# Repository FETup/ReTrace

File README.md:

# ReTrace

ReTrace is a watch mod for the infamous Casio F-91W. Inspired by [CarrotIndustries Pluto mod](https://github.com/carrotIndustries/pluto). Borrowed his PCB design as its well done
and tested. Replaced the MSP430 controller with PIC24.

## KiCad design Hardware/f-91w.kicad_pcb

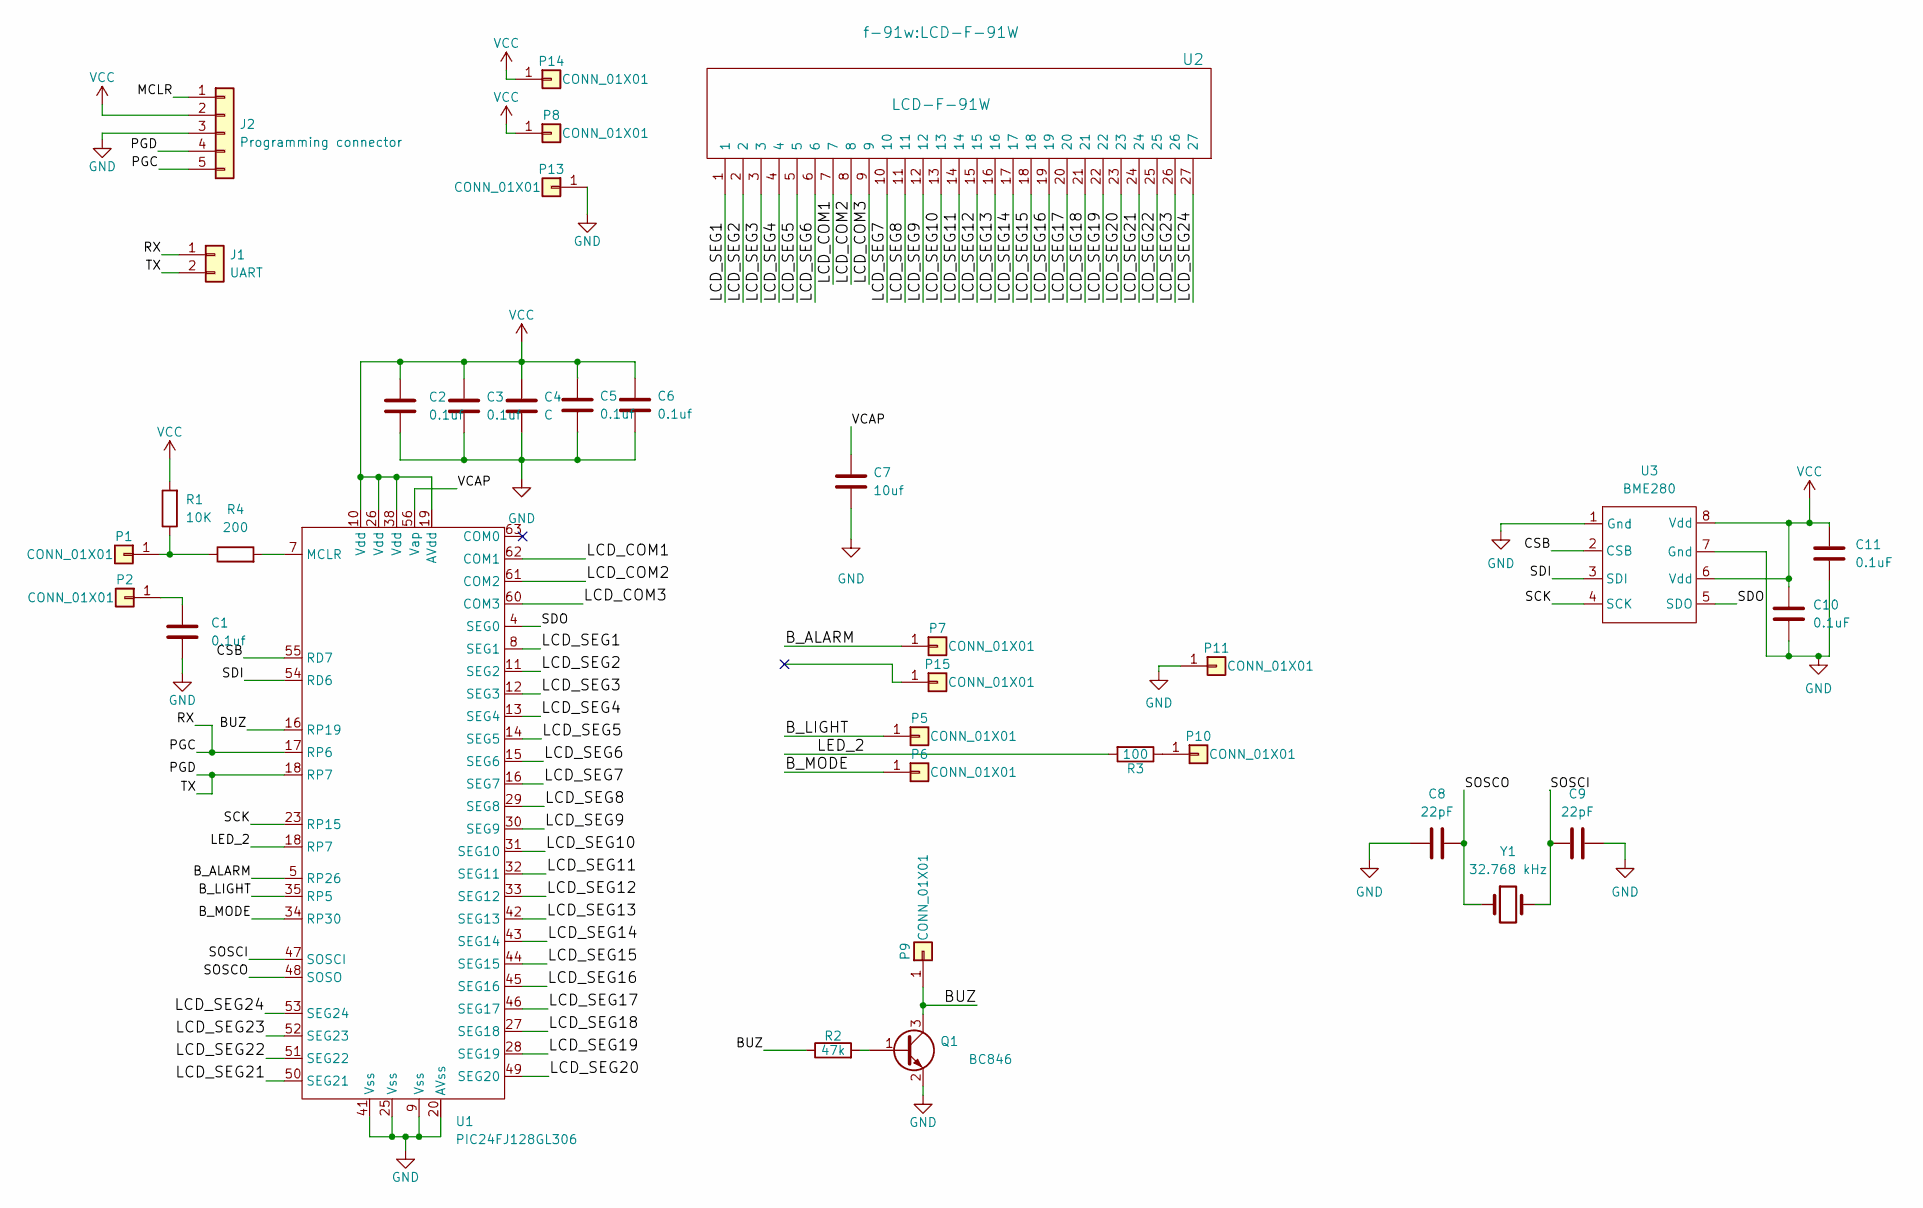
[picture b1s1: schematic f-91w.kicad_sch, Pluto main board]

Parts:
C1, C2, C3, C5, C6: 0.1uf; C_0402_1005Metric
C4: C; C_0402_1005Metric
C7: 10uf; C_0402_1005Metric
C8, C9: 22pF; C_0402_1005Metric
C10, C11: 0.1uF; C_0402_1005Metric
J1: UART; PinHeader_1x02_P1.00mm_Vertical
J2: Programming connector; PinHeader_1x05_P1.00mm_Vertical
P1, P2, P5, P6, P7, P8, P9, P10, P11, P13, P14, P15: CONN_01X01; 1pin
Q1: BC846; SOT-23
R1: 10K; R_0402_1005Metric
R2: 47k; R_0402
R3: 100; R_0402
R4: 200; R_0402_1005Metric
U1: PIC24FJ128GL306; QFN-64-1EP_9x9mm_P0.5mm_EP7.5x7.5mm
U2: LCD-F-91W
U3: BME280; Bosch_LGA-8_2.5x2.5mm_P0.65mm_ClockwisePinNumbering
Y1: 32.768 kHz; Crystal_SMD_EuroQuartz_EQ161-2Pin_3.2x1.5mm

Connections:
/B_ALARM: P7.1, U1.5 (RP26)
/B_LIGHT: P5.1, U1.35 (RP5)
/B_MODE: P6.1, U1.34 (RP30)
/CSB: U1.55 (RD7), U3.2 (CSB)
/LCD_COM1: U1.62 (COM1), U2.7
/LCD_COM2: U1.61 (COM2), U2.8
/LCD_COM3: U1.60 (COM3), U2.9
/LCD_SEG1: U1.8 (SEG1), U2.1
/LCD_SEG2: U1.11 (SEG2), U2.2
/LCD_SEG3: U1.12 (SEG3), U2.3
/LCD_SEG4: U1.13 (SEG4), U2.4
/LCD_SEG5: U1.14 (SEG5), U2.5
/LCD_SEG6: U1.15 (SEG6), U2.6
/LCD_SEG8: U1.29 (SEG8), U2.11
/LCD_SEG9: U1.30 (SEG9), U2.12
/LCD_SEG10: U1.31 (SEG10), U2.13
/LCD_SEG11: U1.32 (SEG11), U2.14
/LCD_SEG12: U1.33 (SEG12), U2.15
/LCD_SEG13: U1.42 (SEG13), U2.16
/LCD_SEG14: U1.43 (SEG14), U2.17
/LCD_SEG15: U1.44 (SEG15), U2.18
/LCD_SEG16: U1.45 (SEG16), U2.19
/LCD_SEG17: U1.46 (SEG17), U2.20
/LCD_SEG18: U1.27 (SEG18), U2.21
/LCD_SEG19: U1.28 (SEG19), U2.22
/LCD_SEG20: U1.49 (SEG20), U2.23
/LCD_SEG21: U1.50 (SEG21), U2.24
/LCD_SEG22: U1.51 (SEG22), U2.25
/LCD_SEG23: U1.52 (SEG23), U2.26
/LCD_SEG24: U1.53 (SEG24), U2.27
/MCLR: J2.1
/PGC: J1.1, J2.5, U1.17 (RP6)
/SCK: U1.23 (RP15), U3.4 (SCK)
/SDI: U1.54 (RD6), U3.3 (SDI)
/SDO: U1.4 (SEG0), U3.5 (SDO)
/SOSCI: C9.1, U1.47 (SOSCI), Y1.2
/SOSCO: C8.2, U1.48 (SOSO), Y1.1
/VCAP: C7.1, U1.56 (Vap)
GND: C1.2, C2.2, C3.2, C4.2, C5.2, C6.2, C7.2, C8.1, C9.2, C10.2, C11.2, J2.3, P11.1, P13.1, Q1.2 (E), U1.9 (Vss), U1.20 (AVss), U1.25 (Vss), U1.41 (Vss), U3.1 (Gnd), U3.7 (Gnd)
unnamed: C1.1, P2.1
unnamed: P1.1, R1.1, R4.1
unnamed: P10.1, R3.1
unnamed: Q1.1 (B), R2.2
unnamed: R4.2, U1.7 (MCLR)
VCC: C2.1, C3.1, C4.1, C5.1, C6.1, C10.1, C11.1, J2.2, P8.1, P14.1, R1.2, U1.10 (Vdd), U1.19 (AVdd), U1.26 (Vdd), U1.38 (Vdd), U3.6 (Vdd), U3.8 (Vdd)

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
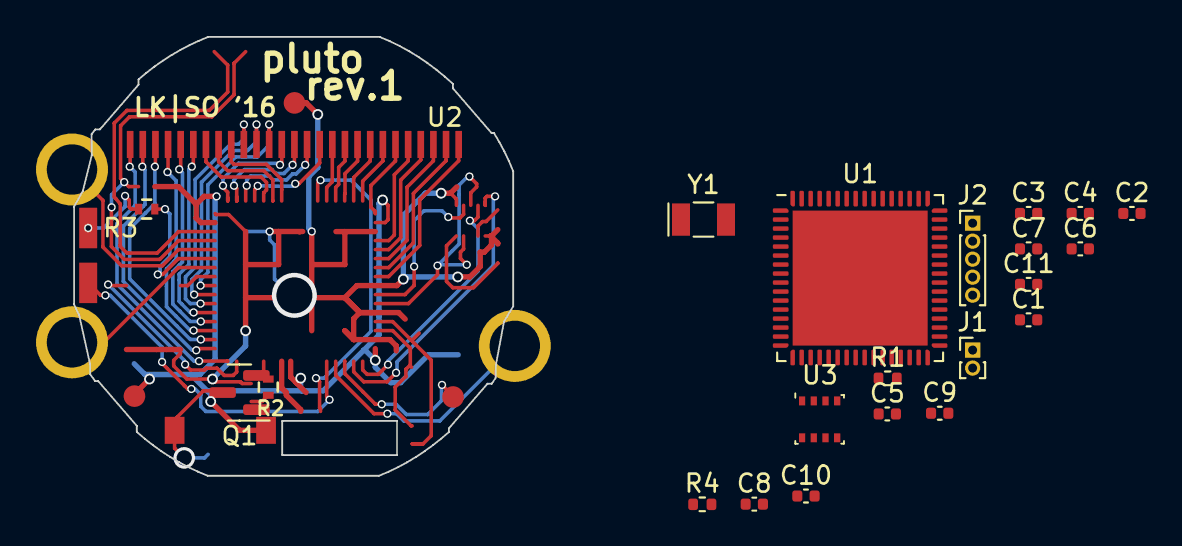
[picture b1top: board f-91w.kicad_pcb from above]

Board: 2 copper layers, 24.4 x 24.4 mm, 32 parts (0 on the bottom side), 46 nets.

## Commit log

2022-06-17 Update Schematic and Add PIC and BME280 symbols
2022-06-19 Add PIC and BME in schematic
2022-06-20 Add temporary symbols to check
2022-06-21 Add BME280 footprint
2022-06-22 Update BOM, schematic and footprint.
